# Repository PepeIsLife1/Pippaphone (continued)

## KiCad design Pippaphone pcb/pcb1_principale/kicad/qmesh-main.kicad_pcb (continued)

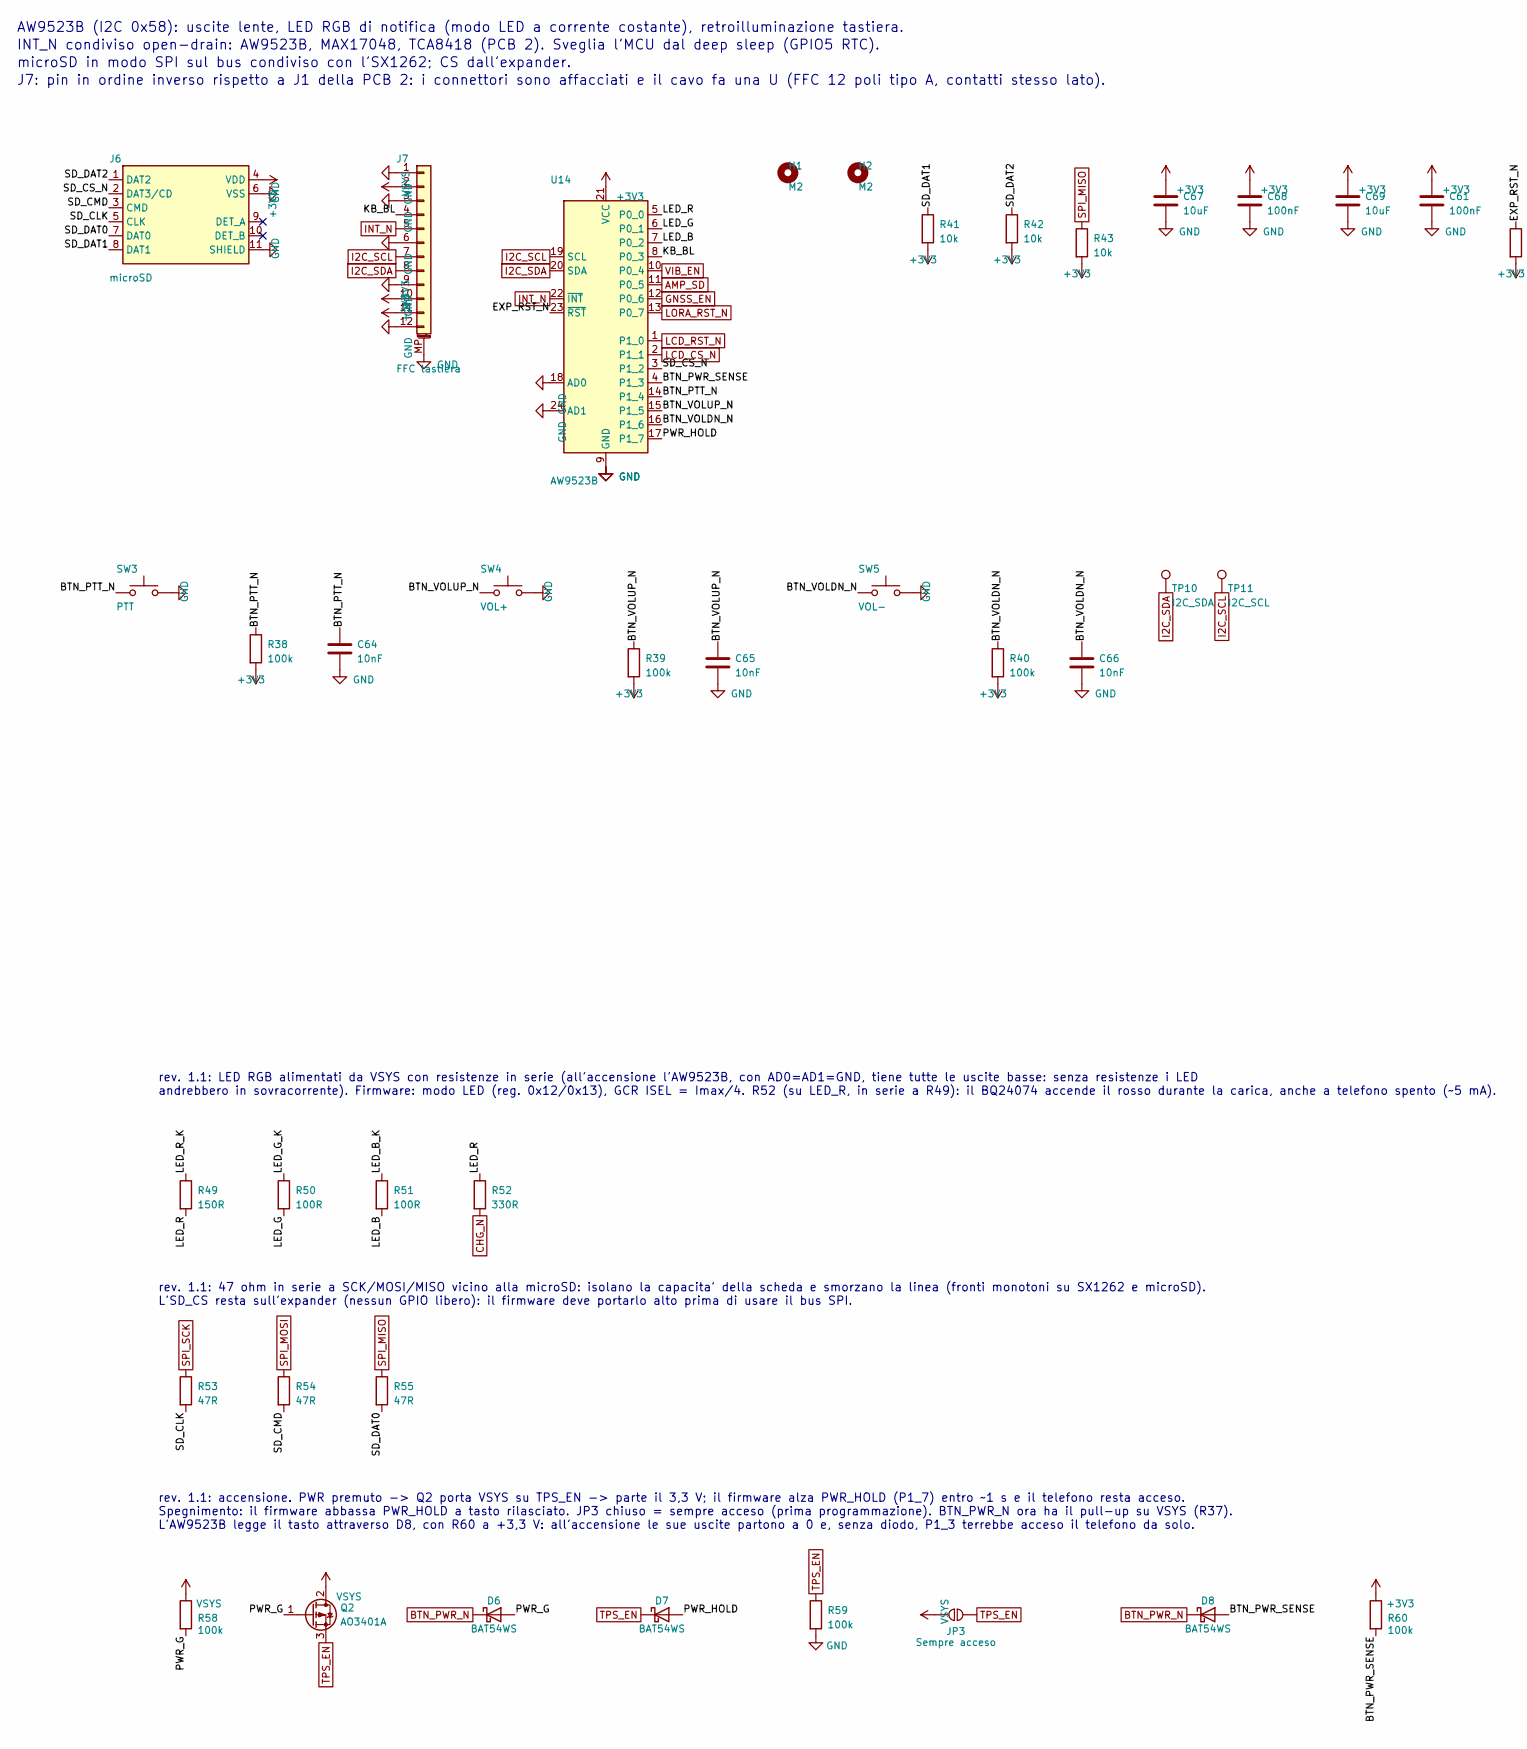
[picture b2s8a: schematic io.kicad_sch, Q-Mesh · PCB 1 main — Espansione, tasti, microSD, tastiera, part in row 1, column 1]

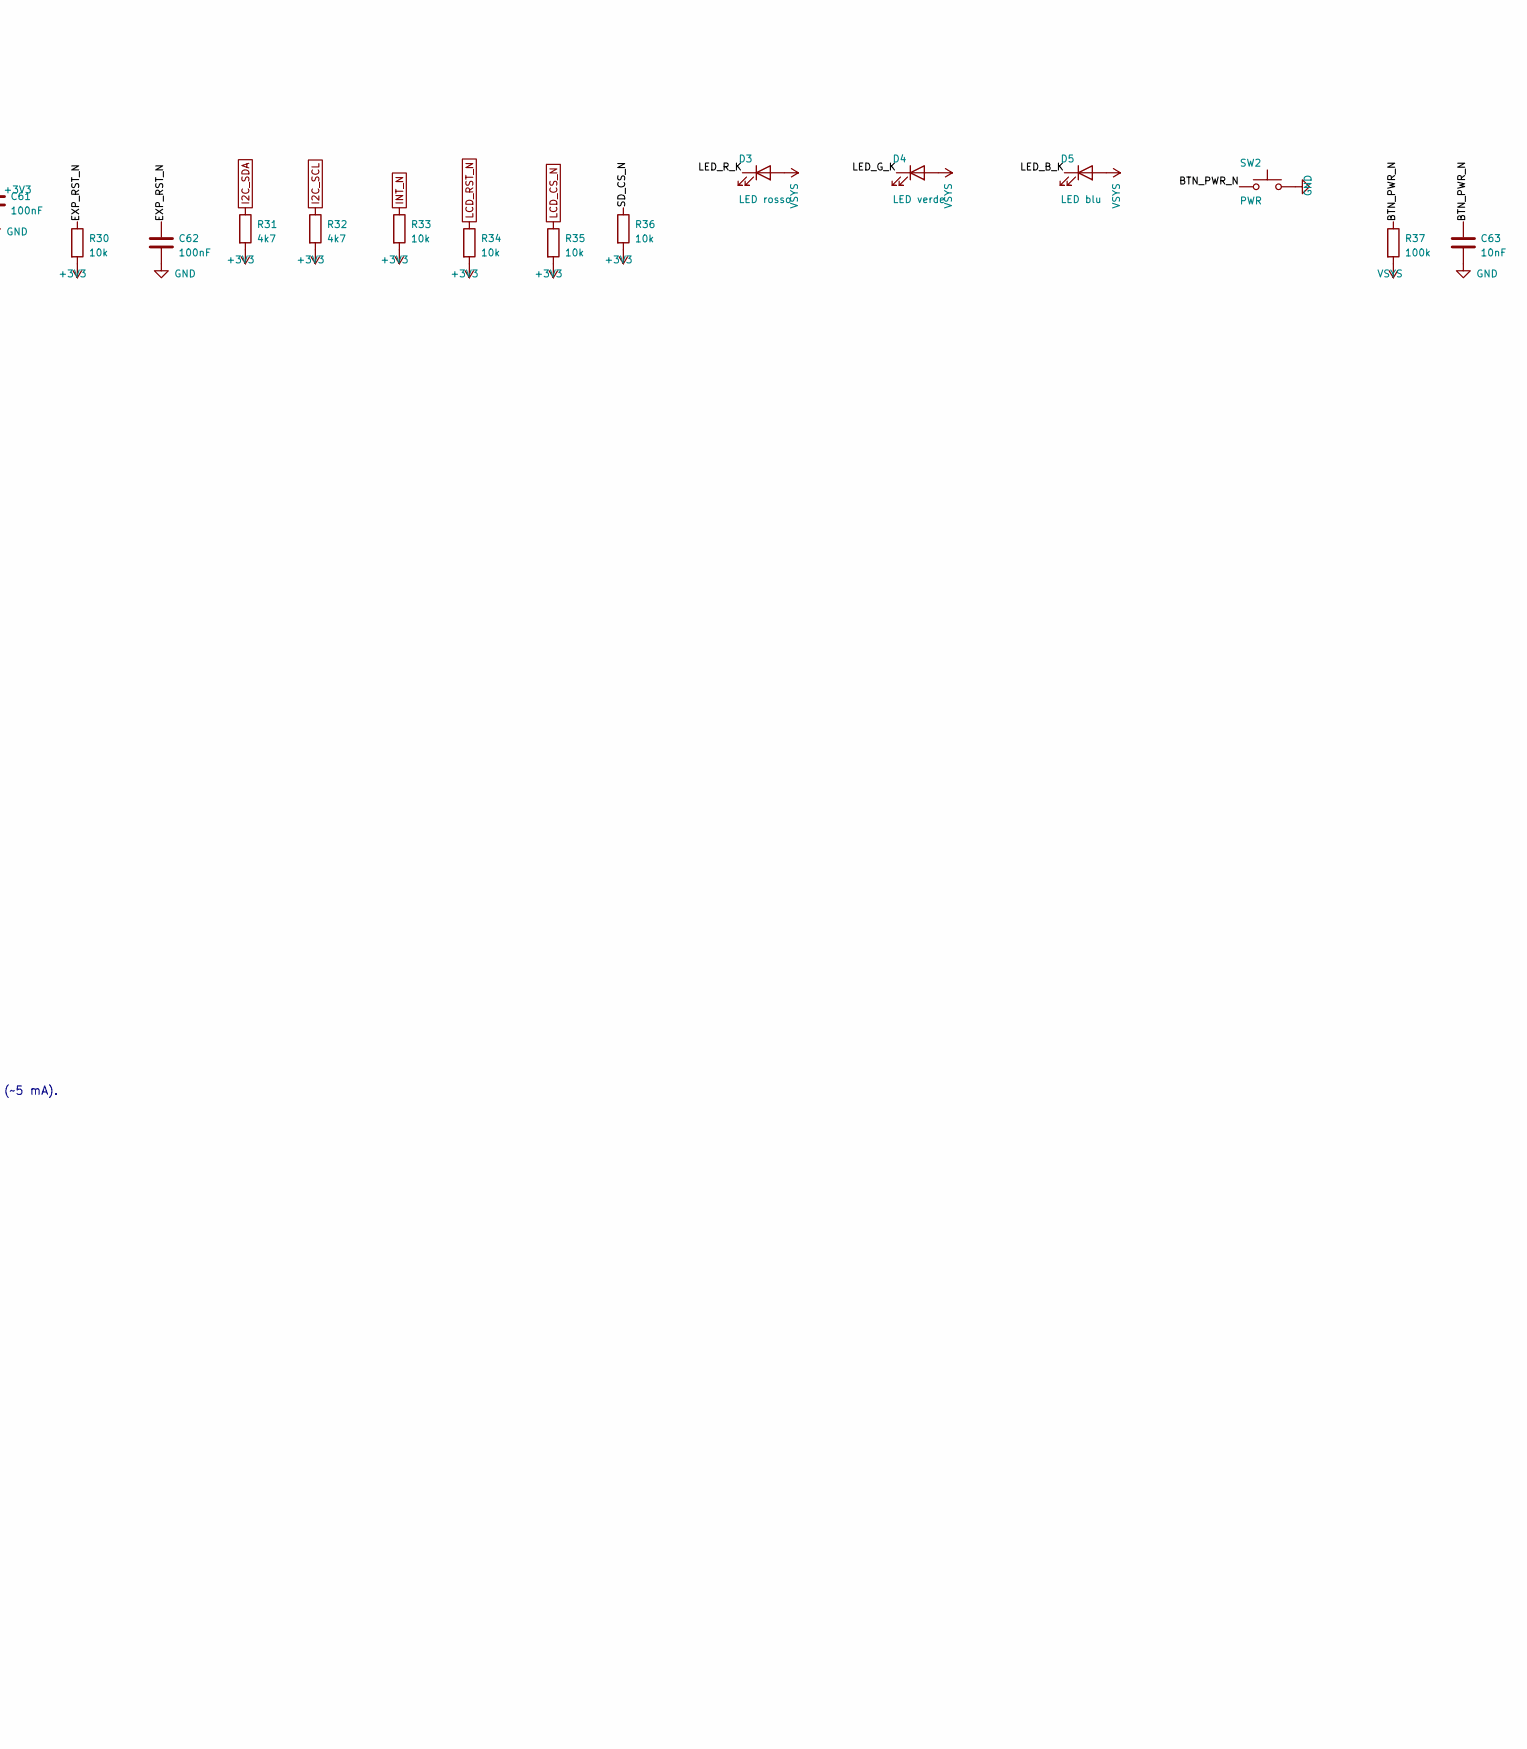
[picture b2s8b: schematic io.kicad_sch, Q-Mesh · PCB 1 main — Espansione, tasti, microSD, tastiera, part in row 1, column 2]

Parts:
C61, C62, C68: 100nF; C_0402_1005Metric
C63, C64, C65, C66: 10nF; C_0402_1005Metric
C67, C69: 10uF; C_0603_1608Metric
D3: LED rosso; LED_0402_1005Metric; MPN XL-1005SURC
D4: LED verde; LED_0402_1005Metric; MPN XL-1005UGC
D5: LED blu; LED_0402_1005Metric; MPN XL-1005UBC
D6, D7, D8: BAT54WS; D_SOD-323; MPN BAT54WS
H1, H2: M2; MountingHole_2.2mm_M2
J6: microSD; microSD_HC_Molex_104031-0811; MPN Molex 104031-0811
J7: FFC tastiera; Hirose_FH12-12S-0.5SH_1x12-1MP_P0.50mm_Horizontal; MPN Hirose FH12-12S-0.5SH(55)
JP3: Sempre acceso; SolderJumper_2_Open_1.0x1.5mm
Q2: AO3401A; SOT-23; MPN AO3401A
R30, R33, R34, R35, R36, R41, R42, R43: 10k; R_0402_1005Metric
R31, R32: 4k7; R_0402_1005Metric
R37, R38, R39, R40: 100k; R_0402_1005Metric
R49: 150R; R_0402_1005Metric; MPN 0402WGF1500TCE
R50, R51: 100R; R_0402_1005Metric; MPN 0402WGF1000TCE
R52: 330R; R_0402_1005Metric; MPN 0402WGF3300TCE
R53, R54, R55: 47R; R_0402_1005Metric; MPN 0402WGF470JTCE
R58, R59, R60: 100k; R_0402_1005Metric; MPN 0402WGF1003TCE
SW2: PWR; SW_SPST_EVQP7C; MPN Panasonic EVQ-P7C01P
SW3: PTT; SW_SPST_EVQP7C; MPN Panasonic EVQ-P7C01P
SW4: VOL+; SW_SPST_EVQP7C; MPN Panasonic EVQ-P7C01P
SW5: VOL-; SW_SPST_EVQP7C; MPN Panasonic EVQ-P7C01P
TP10: I2C_SDA; TestPoint_Pad_D1.0mm
TP11: I2C_SCL; TestPoint_Pad_D1.0mm
U14: AW9523B; QFN-24-1EP_4x4mm_P0.5mm_EP2.7x2.7mm; MPN AW9523BTQR

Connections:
+3V3: C61.1, C67.1, C68.1, C69.1, J6.4 (VDD), J7.10, J7.11, R30.2, R31.2, R32.2, R33.2, R34.2, R35.2, R36.2, R38.2, R39.2, R40.2, R41.2, R42.2, R43.2, R60.1, U14.21 (VCC); also elsewhere on the board
AMP_SD: U14.11 (P0_5); also elsewhere on the board
BTN_PTT_N: C64.1, R38.1, SW3.1, U14.14 (P1_4)
BTN_PWR_N: C63.1, D6.1 (K), D8.1 (K), R37.1, SW2.1
BTN_PWR_SENSE: D8.2 (A), R60.2, U14.4 (P1_3)
BTN_VOLDN_N: C66.1, R40.1, SW5.1, U14.16 (P1_6)
BTN_VOLUP_N: C65.1, R39.1, SW4.1, U14.15 (P1_5)
CHG_N: R52.2; also elsewhere on the board
EXP_RST_N: C62.1, R30.1, U14.23 (~RST)
GND: C61.2, C62.2, C63.2, C64.2, C65.2, C66.2, C67.2, C68.2, C69.2, J6.6 (VSS), J6.11 (SHIELD), J7.1, J7.3, J7.6, J7.9, J7.12, J7.MP (MountPin), R59.2, SW2.2, SW3.2, SW4.2, SW5.2, U14.9 (GND), U14.18 (AD0), U14.24 (AD1), U14.25 (GND); also elsewhere on the board
GNSS_EN: U14.12 (P0_6); also elsewhere on the board
I2C_SCL: J7.7, R32.1, TP11.1, U14.19 (SCL); also elsewhere on the board
I2C_SDA: J7.8, R31.1, TP10.1, U14.20 (SDA); also elsewhere on the board
INT_N: J7.5, R33.1, U14.22 (~INT); also elsewhere on the board
KB_BL: J7.4, U14.8 (P0_3)
LCD_CS_N: R35.1, U14.2 (P1_1); also elsewhere on the board
LCD_RST_N: R34.1, U14.1 (P1_0); also elsewhere on the board
LED_B: R51.2, U14.7 (P0_2)
LED_B_K: D5.1 (K), R51.1
LED_G: R50.2, U14.6 (P0_1)
LED_G_K: D4.1 (K), R50.1
LED_R: R49.2, R52.1, U14.5 (P0_0)
LED_R_K: D3.1 (K), R49.1
LORA_RST_N: U14.13 (P0_7); also elsewhere on the board
PWR_G: D6.2 (A), Q2.1 (G), R58.2
PWR_HOLD: D7.2 (A), U14.17 (P1_7)
SD_CLK: J6.5 (CLK), R53.2
SD_CMD: J6.3 (CMD), R54.2
SD_CS_N: J6.2 (DAT3/CD), R36.1, U14.3 (P1_2)
SD_DAT0: J6.7 (DAT0), R55.2
SD_DAT1: J6.8 (DAT1), R41.1
SD_DAT2: J6.1 (DAT2), R42.1
SPI_MISO: R43.1, R55.1; also elsewhere on the board
SPI_MOSI: R54.1; also elsewhere on the board
SPI_SCK: R53.1; also elsewhere on the board
TPS_EN: D7.1 (K), JP3.2 (B), Q2.3 (D), R59.1; also elsewhere on the board
VIB_EN: U14.10 (P0_4); also elsewhere on the board
VSYS: D3.2 (A), D4.2 (A), D5.2 (A), J7.2, JP3.1 (A), Q2.2 (S), R37.2, R58.1; also elsewhere on the board

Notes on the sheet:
AW9523B (I2C 0x58): uscite lente, LED RGB di notifica (modo LED a corrente costante), retroilluminazione tastiera.
INT_N condiviso open-drain: AW9523B, MAX17048, TCA8418 (PCB 2). Sveglia l'MCU dal deep sleep (GPIO5 RTC).
microSD in modo SPI sul bus condiviso con l'SX1262; CS dall'expander.
J7: pin in ordine inverso rispetto a J1 della PCB 2: i connettori sono affacciati e il cavo fa una U (FFC 12 poli tipo A, contatti stesso lato).
rev. 1.1: LED RGB alimentati da VSYS con resistenze in serie (all'accensione l'AW9523B, con AD0=AD1=GND, tiene tutte le uscite basse: senza resistenze i LED andrebbero in sovracorrente). Firmware: modo LED (reg. 0x12/0x13), GCR ISEL = Imax/4. R52 (su LED_R, in serie a R49): il BQ24074 accende il ro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
rev. 1.1: 47 ohm in serie a SCK/MOSI/MISO vicino alla microSD: isolano la capacita' della scheda e smorzano la linea (fronti monotoni su SX1262 e microSD). L'SD_CS resta sull'expander (nessun GPIO libero): il firmware deve portarlo alto prima di usare il bus SPI.
rev. 1.1: accensione. PWR premuto -> Q2 porta VSYS su TPS_EN -> parte il 3,3 V; il firmware alza PWR_HOLD (P1_7) entro ~1 s e il telefono resta acceso. Spegnimento: il firmware abbassa PWR_HOLD a tasto rilasciato. JP3 chiuso = sempre acceso (prima programmazione). BTN_PWR_N ora ha il pull-up su VSY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

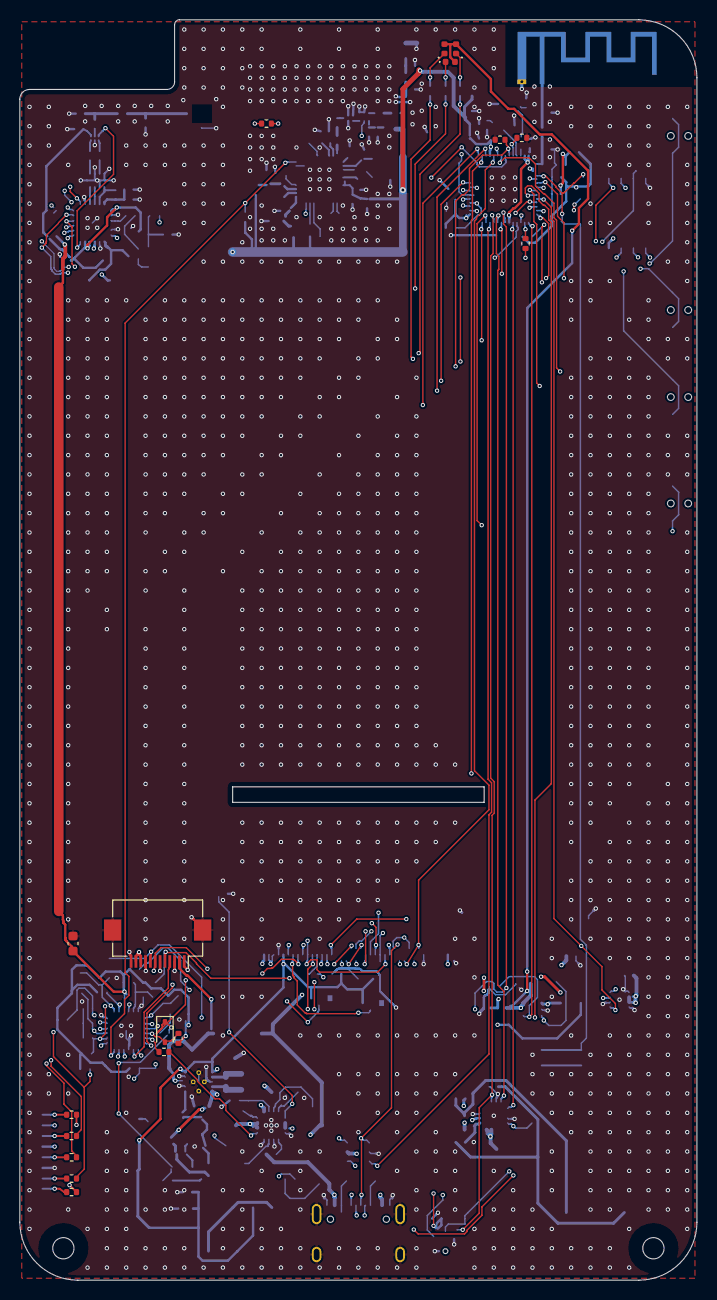
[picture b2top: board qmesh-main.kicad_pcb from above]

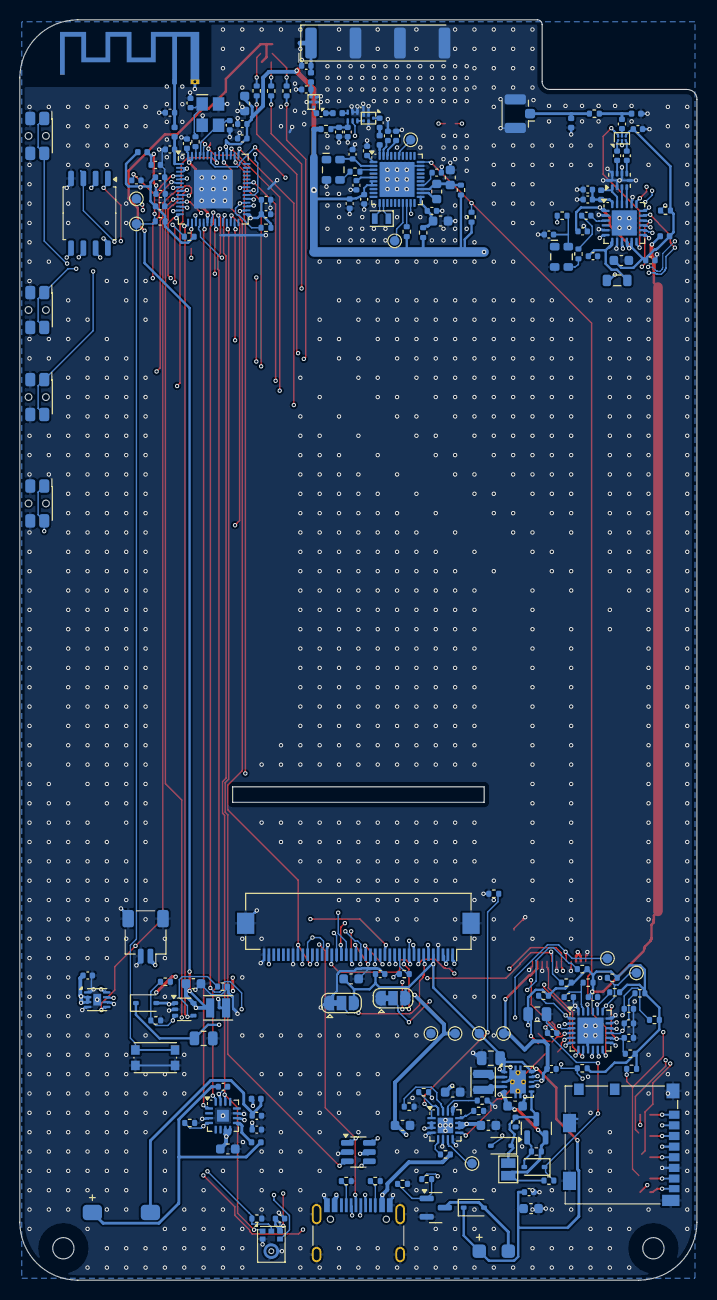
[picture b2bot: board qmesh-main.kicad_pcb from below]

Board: 4 copper layers, 70.0 x 130.3 mm, 205 parts (186 on the bottom side), 152 nets.

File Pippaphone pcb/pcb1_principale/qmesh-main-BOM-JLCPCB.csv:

Comment,Designator,Footprint,MPN,LCSC Part #,Quantity,Note
SR4G013 GNSS,AE2,Antenova_SR4G013_GPS,Antenova SR4G013,,1,Global Sourcing JLCPCB (DigiKey/Mouser)
1uF,"C1,C59",C_0603_1608Metric,CL10A105KB8NNNC,C15849,2,
10uF,"C2,C4,C11,C24,C52,C57,C67,C69",C_0603_1608Metric,CL10A106KP8NNNC,C19702,8,
4.7uF,"C3,C36,C37",C_0603_1608Metric,CL10A475KO8NNNC,C19666,3,
100nF,"C5,C9,C13,C14,C17,C18,C25,C26,C28,C31,C43,C44,C46,C53,C56,C58,C61,C62,C68",C_0402_1005Metric,CL05B104KO5NNNC,C1525,19,
22uF,"C6,C7",C_0805_2012Metric,CL21A226MAQNNNE,C45783,2,
1uF,"C8,C10,C12,C15,C19,C38,C39,C40,C41,C42,C45,C71",C_0402_1005Metric,CL05A105KA5NQNC,C52923,12,
10nF,"C16,C63,C64,C65,C66",C_0402_1005Metric,CL05B103KB5NNNC,C15195,5,
12pF,"C20,C21",C_0402_1005Metric,0402CG120J500NT,C1547,2,
470nF,C27,C_0402_1005Metric,CL05A474KP5NNNC,C47339,1,
10pF,C29,C_0402_1005Metric,CL05C100JB5NNNC,C32949,1,
47pF,C30,C_0402_1005Metric,0402CG470J500NT,C1567,1,
100pF,"C32,C33,C34,C35,C51",C_0402_1005Metric,0402CG101J500NT,C1546,5,
470pF,C50,C_0402_1005Metric,CC0402JRNPO9BN471,C106259,1,
220pF,"C54,C55",C_0402_1005Metric,0402B221K500NT,C1530,2,
1uF 50V,C60,C_0805_2012Metric,CL21B105KBFNNNE,C28323,1,
BAT54,"D1,D6,D7,D8",D_SOD-323,BAT54WS-7-F,C124205,4,
B0540WS,D2,D_SOD-323,B0540WS SF,C22635,1,
LED rosso,D3,LED_0402_1005Metric,XL-1005SURC,C25503345,1,
LED verde,D4,LED_0402_1005Metric,XL-1005UGC,C965793,1,
LED blu,D5,LED_0402_1005Metric,XL-1005UBC,C22355736,1,
600R@100MHz,FB1,L_0402_1005Metric,BLM15AG601SN1D,C76884,1,
FB 600R@100MHz,"FB2,FB3",L_0402_1005Metric,BLM15PX601SN1D,C160977,2,
SAW 1575MHz,"FL1,FL2",Filter_1411-5_1.4x1.1mm,B39162B4327P810,C2650956,2,
USB-C,J1,USB_C_Receptacle_HRO_TYPE-C-31-M-12,HRO TYPE-C-31-M-12,C165948,1,
BATT,J2,JST_SH_SM02B-SRSS-TB_1x02-1MP_P1.00mm_Horizontal,JST SM02B-SRSS-TB,C160402,1,
U.FL antenna LoRa,J4,U.FL_Hirose_U.FL-R-SMT-1_Vertical,U.FL-R-SMT-1(80),C88374,1,
LCD 40P 0.5mm,J5,Hirose_FH12-40S-0.5SH_1x40-1MP_P0.50mm_Horizontal,Hirose FH12A-40S-0.5SH(55),C506795,1,
microSD,J6,microSD_HC_Molex_104031-0811,Molex 104031-0811,C585350,1,
FFC tastiera,J7,Hirose_FH12-12S-0.5SH_1x12-1MP_P0.50mm_Horizontal,Hirose FH12-12S-0.5SH(55),C88360,1,
2.2uH,L1,L_Changjiang_FNR252012S,FTC252012S2R2MBCA,C5832372,1,
2.0nH,L2,L_0402_1005Metric,LQG15HS2N0S02D,C18216,1,
0R/tune,"L3,L9",L_0402_1005Metric,0402WGF0000TCE,C17168,2,
15uH,L4,L_0805_2012Metric,MLZ2012N150LT000,C531290,1,
47nH,L5,L_0402_1005Metric,LQG15HS47NJ02D,C97998,1,
56nH ESD,L6,L_0402_1005Metric,LQG15HS56NJ02D,C162544,1,
4.3nH,L10,L_0402_1005Metric,LQG15HS4N3S02D,C97999,1,
10uH,L12,L_Changjiang_FNR252012S,FTC252012S100MBCA,C5832376,1,
AO3400A,Q1,SOT-23,AO3400A,C20917,1,
5k1,"R1,R2",R_0402_1005Metric,0402WGF5101TCE,C25905,2,
1k0 1%,R3,R_0402_1005Metric,0402WGF1001TCE,C11702,1,
1k1 1%,R4,R_0402_1005Metric,0402WGF1101TCE,C25860,1,
47k,"R5,R16",R_0402_1005Metric,0402WGF4702TCE,C25792,2,
10k,"R8,R10,R11,R12,R13,R14,R20,R30,R33,R34,R35,R36,R41,R42,R43",R_0402_1005Metric,0402WGF1002TCE,C25744,15,
100k,"R21,R22,R23,R25,R29,R37,R38,R39,R40,R58,R59,R60",R_0402_1005Metric,0402WGF1003TCE,C25741,12,
0R,"R15,R17,R18,R45,R46",R_0402_1005Metric,0402WGF0000TCE,C17168,5,
220R,R48,R_0402_1005Metric,0402WGF2200TCE,C25091,1,
100R,"R24,R50,R51",R_0402_1005Metric,0402WGF1000TCE,C25076,3,
47R,"R26,R53,R54,R55,R56,R57",R_0402_1005Metric,0402WGF470JTCE,C25118,6,
10R 1%,"R27,R28,R44",R_0402_1005Metric,0402WGF100JTCE,C25077,3,
4k7,"R31,R32",R_0402_1005Metric,0402WGF4701TCE,C25900,2,
RESET,SW1,SW_Push_1P1T_NO_CK_KMR2,KMR221GLFS,C72443,1,
EVQ-P7C01P,"SW2,SW3,SW4,SW5",SW_SPST_EVQP7C,Panasonic EVQ-P7C01P,C388883,4,
USBLC6-2SC6,U1,SOT-23-6,USBLC6-2SC6,C7519,1,
BQ24074RGT,U2,VQFN-16-1EP_3x3mm_P0.5mm_EP1.6x1.6mm,BQ24074RGTR,C54313,1,
TPS63001,U3,Texas_DRC0010J_ThermalVias,TPS63001DRCR,C28060,1,
MAX17048,U4,TDFN-8-1EP_2x2mm_P0.5mm_EP0.8x1.2mm,MAX17048G+T10,C2682616,1,
ESP32-S3R8,U5,QFN-56-1EP_7x7mm_P0.4mm_EP4x4mm,ESP32-S3R8,C2913194,1,
W25Q128JVSIQ,U6,SOIC-8_5.23x5.23mm_P1.27mm,W25Q128JVSIQ,C97521,1,
SX1262IMLTRT,U7,QFN-24-1EP_4x4mm_P0.5mm_EP2.6x2.6mm,SX1262IMLTRT,C191341,1,
0900FM15K0039,U8,Balun_Johanson_0900FM15K0039,0900FM15K0039001E,C7434807,1,
BGS12WN6,U9,Infineon_PG-TSNP-6-10_0.7x1.1mm_0.7x1.1mm_P0.4mm,BGS12WN6E6327XTSA1,C534203,1,
AT6558R,U10,QFN-40-1EP_5x5mm_P0.4mm_EP3.6x3.6mm,AT6558R-5N32,C500608,1,
MAX98357A,U11,TQFN-16-1EP_3x3mm_P0.5mm_EP1.23x1.23mm,MAX98357AETE+T,C910544,1,
ICS-43434,U12,InvenSense_ICS-43434-6_3.5x2.65mm,ICS-43434,C5656610,1,
TPS61169,U13,SOT-353_SC-70-5,TPS61169DCKR,C71045,1,
AW9523B,U14,QFN-24-1EP_4x4mm_P0.5mm_EP2.7x2.7mm,AW9523BTQR,C148077,1,
40MHz 10pF,Y1,Crystal_SMD_3225-4Pin_3.2x2.5mm,SX3B40.000F1010F30,C7302016,1,
TCXO 32MHz 1.8V,Y2,Oscillator_SMD_SeikoEpson_TG2520SMN-xxx-xxxxxx-4Pin_2.5x2.0mm,X1G0054210205,C7527388,1,
TCXO 26MHz 0.5ppm,Y3,Oscillator_SMD_SeikoEpson_TG2520SMN-xxx-xxxxxx-4Pin_2.5x2.0mm,2T026000VY,C19725361,1,
33nF,C70,C_0402_1005Metric,CL05B333KO5NNNC,C13594,1,
2.2uH,L8,L_0603_1608Metric,LQM18PN2R2MFRL,C337910,1,
6.8nH,L11,L_0402_1005Metric,LQG15HS6N8J02D,C77110,1,
AT2659 LNA GNSS,U15,AT2659_DFN-6_1.5x1.0mm_P0.5mm,AT2659,C92450,1,
32.768kHz 9pF,Y4,Crystal_SMD_2012-2Pin_2.0x1.2mm,SC-20S 32.768kHz 20PPM 9pF,C97603,1,
NTC 10k B3380,R7,R_0402_1005Metric,NCP15XH103F03RC,C77131,1,
150R,R49,R_0402_1005Metric,0402WGF1500TCE,C25082,1,
330R,R52,R_0402_1005Metric,0402WGF3300TCE,C25104,1,
AO3401A,Q2,SOT-23,AO3401A,C15127,1,

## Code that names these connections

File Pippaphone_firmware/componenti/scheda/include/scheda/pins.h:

// Piedinatura della PCB 1 rev. 1.1 (Pippaphone), ricavata dal file KiCad.
//
// Rev. 1.1: il 3,3 V si accende col tasto PWR e resta acceso finche' PWR_HOLD (P1_7) e' a 1;
// il tasto arriva a P1_3 attraverso D8 (con R60 a +3,3 V); CHG_N del BQ24074 accende solo il
// LED rosso e non e' piu' leggibile (la carica si ricava dal MAX17048).
#pragma once

#include "driver/gpio.h"
#include "sdkconfig.h"

#if CONFIG_SCHEDA_TDECK_PLUS
#include "scheda/pins_tdeck.h"
#else

namespace scheda {

// ---- LoRa SX1262 (bus SPI condiviso con la microSD) ----
constexpr gpio_num_t PIN_SPI_MOSI = GPIO_NUM_11;
constexpr gpio_num_t PIN_SPI_SCK = GPIO_NUM_12;
constexpr gpio_num_t PIN_SPI_MISO = GPIO_NUM_13;
constexpr gpio_num_t PIN_LORA_NSS = GPIO_NUM_8;
constexpr gpio_num_t PIN_LORA_BUSY = GPIO_NUM_7;
constexpr gpio_num_t PIN_LORA_DIO1 = GPIO_NUM_6;
// Reset LoRa: expander P0_7. TCXO a 1,8 V da DIO3, switch RF da DIO2.

// ---- I2C: AW9523B 0x58, MAX17048 0x36, TCA8418 0x34 (PCB 2) ----
constexpr gpio_num_t PIN_I2C_SDA = GPIO_NUM_15;
constexpr gpio_num_t PIN_I2C_SCL = GPIO_NUM_16;
constexpr bool I2C_PULLUP_INTERNE = false;  // pull-up da 4,7k sulla scheda
constexpr gpio_num_t PIN_INT_N = GPIO_NUM_5;  // interruzione condivisa, open drain, sveglia dal deep sleep
constexpr uint8_t ADDR_AW9523 = 0x58;
constexpr uint8_t ADDR_MAX17048 = 0x36;
constexpr uint8_t ADDR_TCA8418 = 0x34;

// ---- Display RGB 480x480 (ST7701S), 12 bit: R3-R5, G0-G5, B3-B5 ----
constexpr gpio_num_t PIN_LCD_VSYNC = GPIO_NUM_0;  // anche strap di boot (pull-up)
constexpr gpio_num_t PIN_LCD_HSYNC = GPIO_NUM_1;
constexpr gpio_num_t PIN_LCD_DE = GPIO_NUM_9;
constexpr gpio_num_t PIN_LCD_PCLK = GPIO_NUM_43;
constexpr gpio_num_t PIN_LCD_R3 = GPIO_NUM_2;
constexpr gpio_num_t PIN_LCD_R4 = GPIO_NUM_42;
constexpr gpio_num_t PIN_LCD_R5 = GPIO_NUM_41;
constexpr gpio_num_t PIN_LCD_G0 = GPIO_NUM_40;
constexpr gpio_num_t PIN_LCD_G1 = GPIO_NUM_39;
constexpr gpio_num_t PIN_LCD_G2 = GPIO_NUM_38;
constexpr gpio_num_t PIN_LCD_G3 = GPIO_NUM_21;
constexpr gpio_num_t PIN_LCD_G4 = GPIO_NUM_47;  // anche SCK della SPI a 3 fili di inizializzazione
constexpr gpio_num_t PIN_LCD_G5 = GPIO_NUM_48;  // anche SDA della SPI a 3 fili
constexpr gpio_num_t PIN_LCD_B3 = GPIO_NUM_3;
constexpr gpio_num_t PIN_LCD_B4 = GPIO_NUM_45;  // strap VDD_SPI (pull-down)
constexpr gpio_num_t PIN_LCD_B5 = GPIO_NUM_46;  // strap (pull-down)
constexpr gpio_num_t PIN_LCD_BL = GPIO_NUM_10;  // PWM verso il TPS61169
// CS e RESET del pannello: expander P1_1 e P1_0.

// ---- Audio I2S: MAX98357A (altoparlante) e ICS-43434 (microfono) sullo stesso bus ----
constexpr gpio_num_t PIN_I2S_BCLK = GPIO_NUM_17;
constexpr gpio_num_t PIN_I2S_WS = GPIO_NUM_18;
constexpr gpio_num_t PIN_I2S_DOUT = GPIO_NUM_14;
constexpr gpio_num_t PIN_I2S_DIN = GPIO_NUM_4;

// ---- GNSS AT6558R: solo uscita NMEA verso l'ESP32 ----
constexpr gpio_num_t PIN_GNSS_RX = GPIO_NUM_44;

// ---- Uscite e ingressi dell'expander AW9523B ----
enum class Exp : uint8_t {
    LED_R = 0,       // P0_0 (modo LED)
    LED_G = 1,       // P0_1 (modo LED)
    LED_B = 2,       // P0_2 (modo LED)
    KB_BL = 3,       // P0_3 retroilluminazione tastiera (modo LED)
    VIB_EN = 4,      // P0_4 motore vibrazione
    AMP_SD = 5,      // P0_5 amplificatore: 1 = acceso (canale sinistro), 0 = spento
    GNSS_EN = 6,     // P0_6 GNSS: 1 = acceso, 0 = standby
    LORA_RST_N = 7,  // P0_7
    LCD_RST_N = 8,   // P1_0
    LCD_CS_N = 9,    // P1_1
    SD_CS_N = 10,    // P1_2
    BTN_PWR_N = 11,  // P1_3 ingresso: BTN_PWR_SENSE (tasto PWR attraverso D8), 0 = premuto
    BTN_PTT_N = 12,  // P1_4 ingresso
    BTN_VOLUP_N = 13,  // P1_5 ingresso
    BTN_VOLDN_N = 14,  // P1_6 ingresso
    PWR_HOLD = 15,   // P1_7 uscita: 1 = tiene acceso il TPS63001 (autoritenuta), 0 = spegne tutto
};

}  // namespace scheda

#endif  // CONFIG_SCHEDA_TDECK_PLUS
